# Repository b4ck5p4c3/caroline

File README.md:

# Project Caroline

Stratum 1 NTP server and clock reference based on surplus Huawei LMPT board.

**TBD**

## License

These licenses apply to this repository, unless otherwise noted:

- [MIT X11 License](./LICENSE) for software, configuration files, and documentation.
- [CERN-OHL-S](./hardware/LICENSE) for hardware design files.

## Acknowledgments

- <https://blog.heypete.com/2016/11/01/note-to-self-raspberry-pi-motorola-oncore-ut-setup/>
- <https://github.com/tiagofreire-pt/rpi_uputronics_stratum1_chrony>

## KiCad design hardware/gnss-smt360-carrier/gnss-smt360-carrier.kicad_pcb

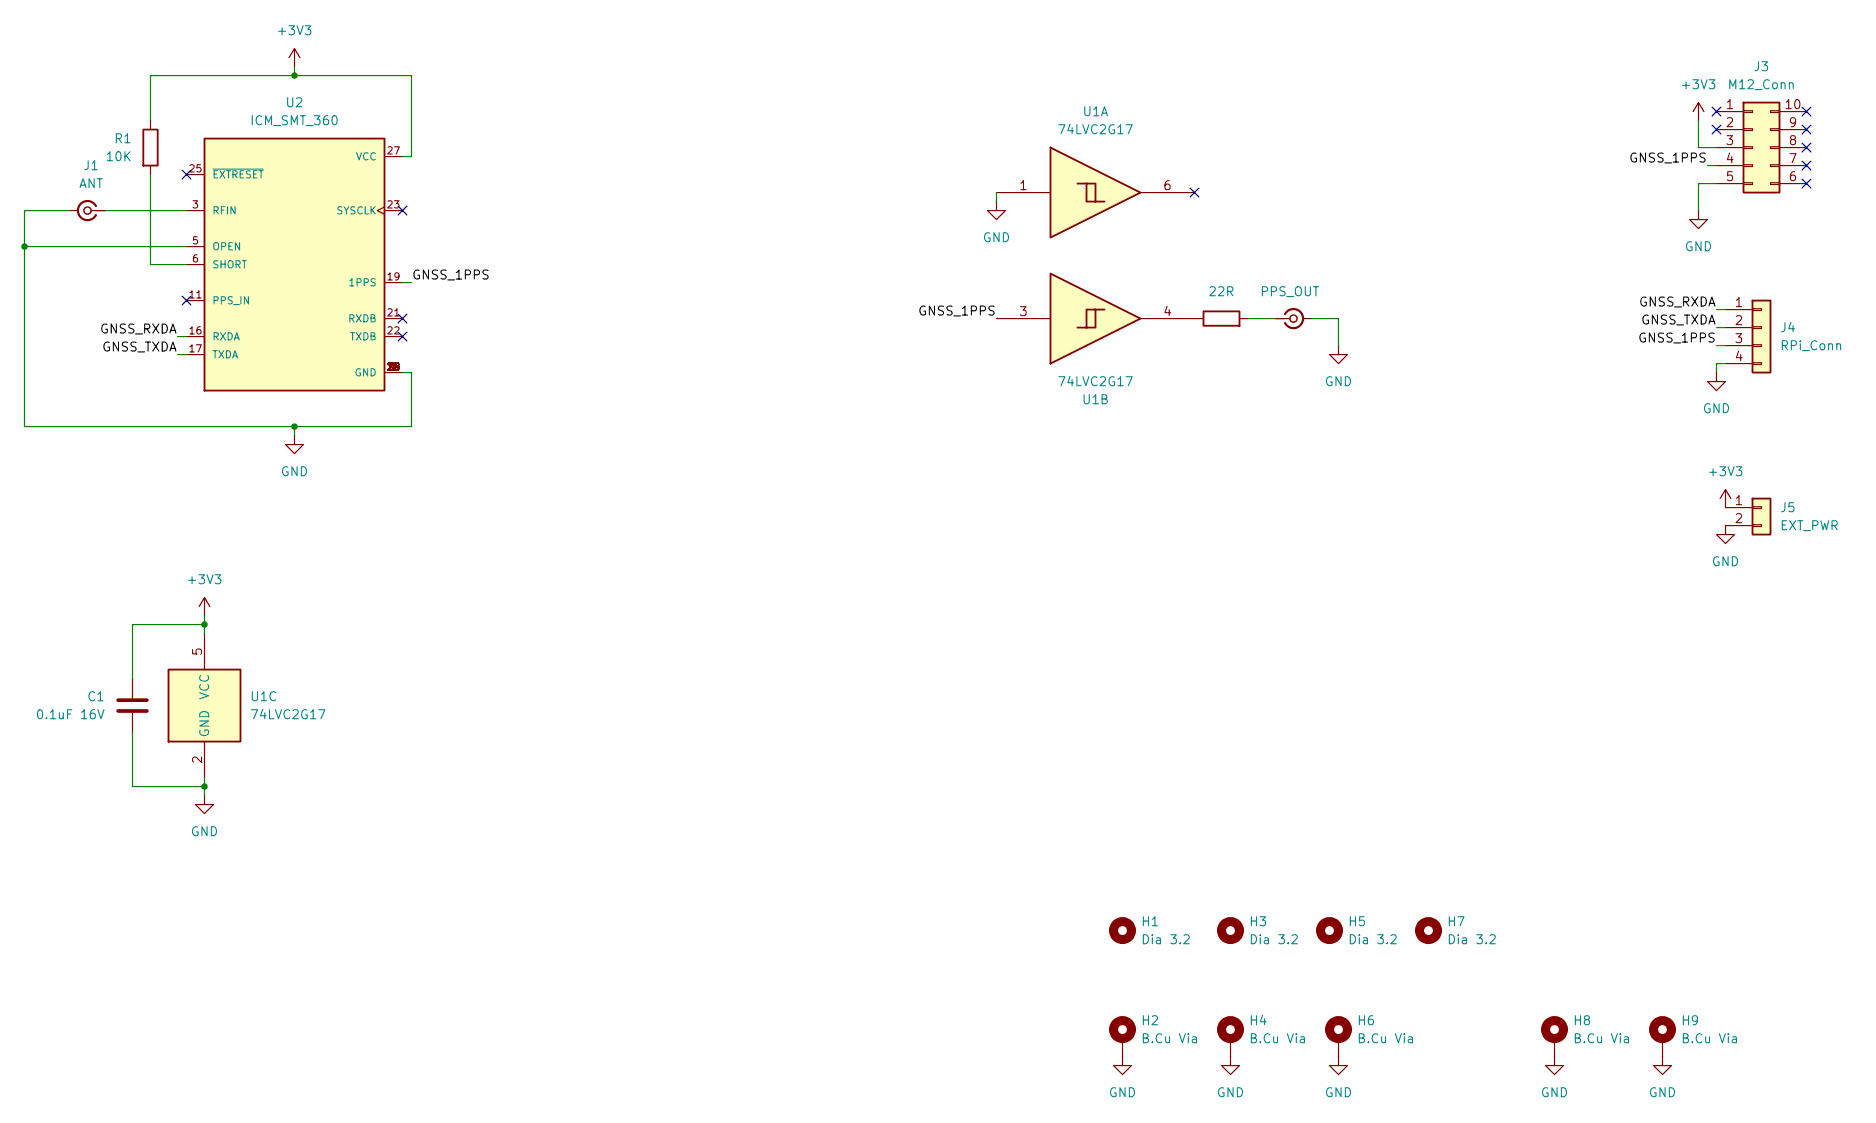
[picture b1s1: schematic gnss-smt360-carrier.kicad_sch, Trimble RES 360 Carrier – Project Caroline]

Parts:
C1: 0.1uF 16V; C_0805_2012Metric
H1, H3, H5, H7: Dia 3.2; MountingHole_3.2mm_M3
H2, H4, H6, H8, H9: B.Cu Via; Hole_Via_0.8mm
J1: ANT; SMA_Molex_73251-2200_Horizontal
J2: PPS_OUT; Connector_RF_UFL_SMT160
J3: M12_Conn; PinHeader_2x05_P1.27mm_Vertical_SMD
J4: RPi_Conn; PinHeader_1x04_P2.54mm_Vertical
J5: EXT_PWR; PinHeader_1x02_P2.54mm_Vertical
R1: 10K; R_0805_2012Metric
R2: 22R; R_0805_2012Metric
U1: 74LVC2G17; SOT-23-6
U2: ICM_SMT_360; RF_GPS_ICM_SMT_360; PARTREV G

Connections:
+3V3: C1.2, J3.3 (+3V_PWR), J5.1, R1.1, U1.5 (VCC), U2.27 (VCC)
/GNSS_1PPS: J3.4 (1PPS), J4.3, U1.3, U2.19 (1PPS)
/GNSS_RXDA: J4.1, U2.16 (RXDA)
/GNSS_TXDA: J4.2, U2.17 (TXDA)
GND: C1.1, H2.1, H4.1, H6.1, H8.1, H9.1, J1.2 (Ext), J2.2 (Ext), J3.5 (GND), J4.4, J5.2, U1.1, U1.2 (GND), U2.1 (GND), U2.2 (GND), U2.4 (GND), U2.5 (OPEN), U2.14 (GND), U2.15 (GND), U2.18 (GND), U2.20 (GND), U2.24 (GND), U2.26 (GND), U2.28 (GND)
unnamed: J1.1 (In), U2.3 (RFIN)
unnamed: J2.1 (In), R2.2
unnamed: R2.1, U1.4
unnamed: R1.2, U2.6 (SHORT)

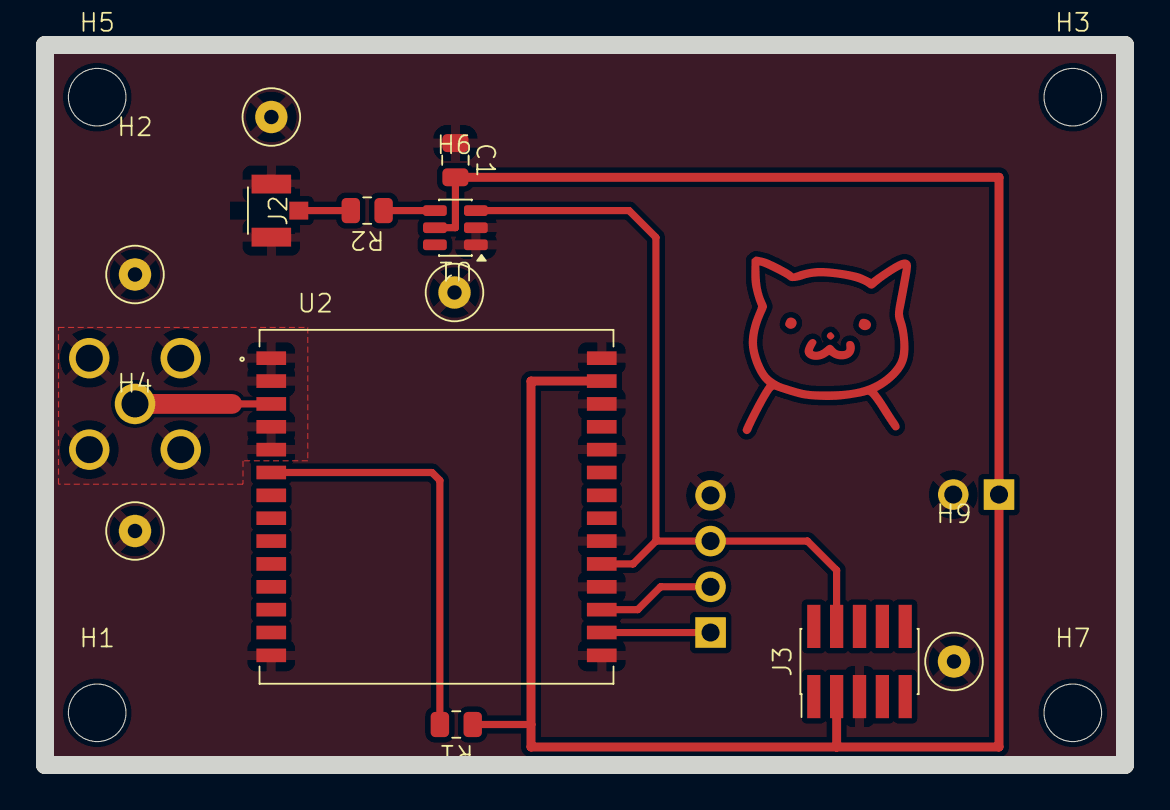
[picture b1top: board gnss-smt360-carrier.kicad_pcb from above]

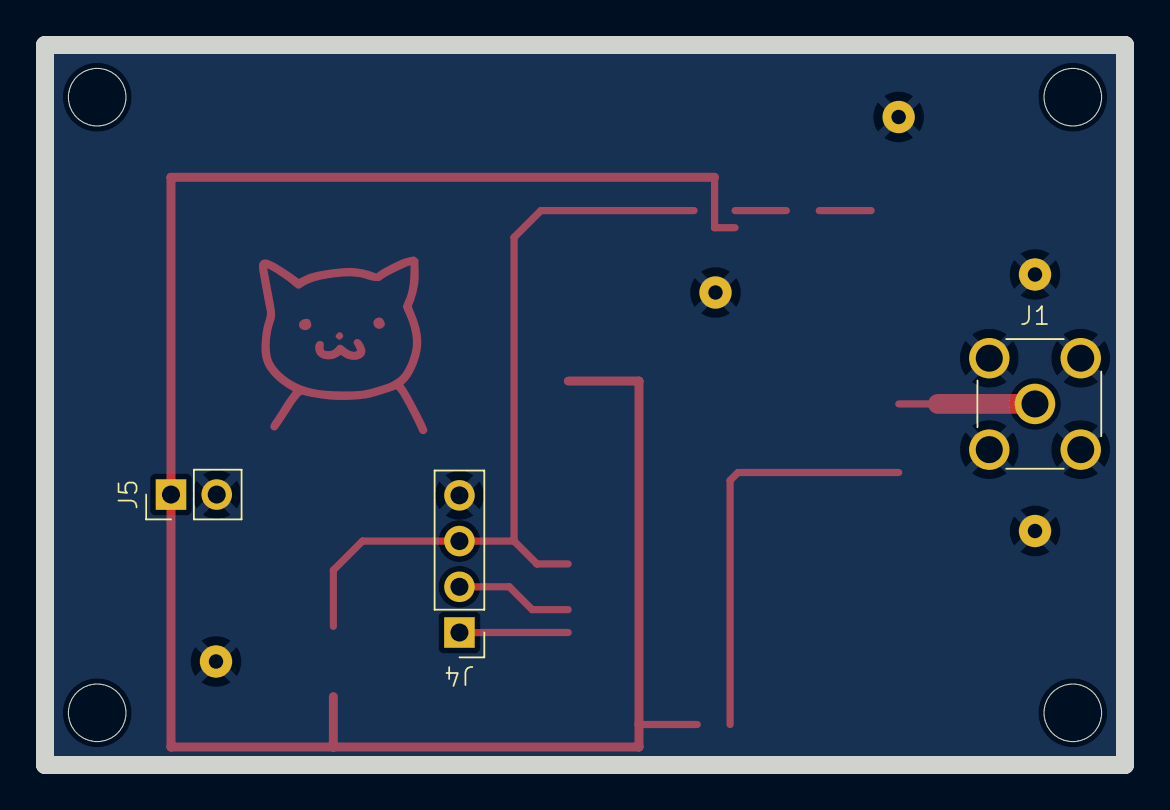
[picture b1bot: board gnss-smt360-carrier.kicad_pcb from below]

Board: 2 copper layers, 60.0 x 40.0 mm, 19 parts (3 on the bottom side), 9 nets.

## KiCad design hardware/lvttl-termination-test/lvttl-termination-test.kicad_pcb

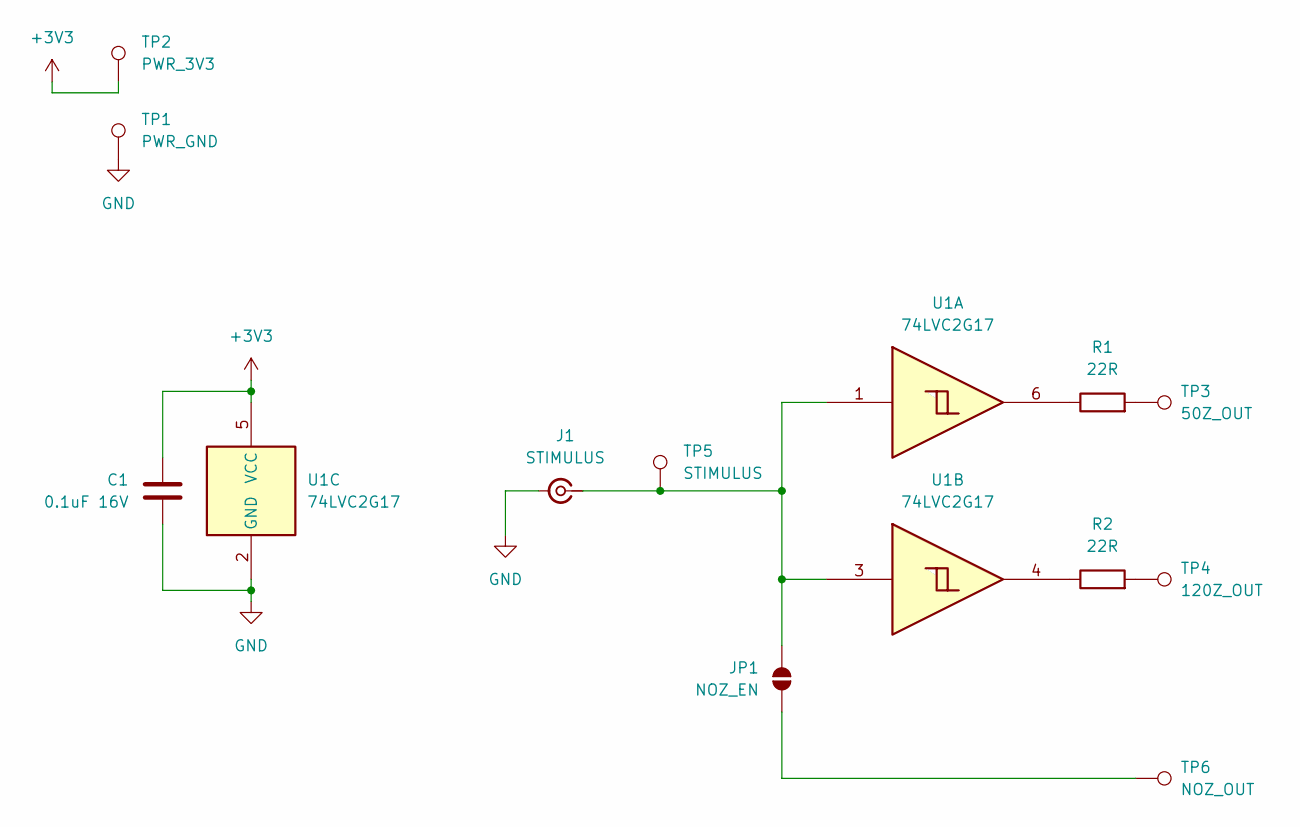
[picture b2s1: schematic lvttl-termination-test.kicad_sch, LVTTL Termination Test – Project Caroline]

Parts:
C1: 0.1uF 16V; C_0805_2012Metric
J1: STIMULUS; SMA_Molex_73251-1153_EdgeMount_Horizontal
JP1: NOZ_EN; SolderJumper-2_P1.3mm_Open_TrianglePad1.0x1.5mm
R1, R2: 22R; R_0805_2012Metric
TP1: PWR_GND; TestPoint_Pad_1.5x1.5mm
TP2: PWR_3V3; TestPoint_Pad_D1.5mm
TP3: 50Z_OUT; TestPoint_Pad_D1.5mm
TP4: 120Z_OUT; TestPoint_Pad_D1.5mm
TP5: STIMULUS; TestPoint_Pad_D1.5mm
TP6: NOZ_OUT; TestPoint_Pad_D1.5mm
U1: 74LVC2G17; SOT-23-6

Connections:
+3V3: C1.1, TP2.1, U1.5 (VCC)
GND: C1.2, J1.2 (Ext), TP1.1, U1.2 (GND)
unnamed: J1.1 (In), JP1.2 (B), TP5.1, U1.1, U1.3
unnamed: JP1.1 (A), TP6.1
unnamed: R1.1, U1.6
unnamed: R1.2, TP3.1
unnamed: R2.1, U1.4
unnamed: R2.2, TP4.1

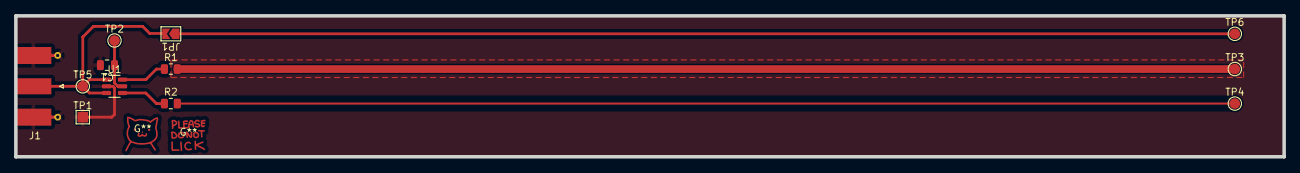
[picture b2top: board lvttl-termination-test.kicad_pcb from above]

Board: 2 copper layers, 180.0 x 20.0 mm, 14 parts (0 on the bottom side), 8 nets.

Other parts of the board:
G**: Cat; Flo_Cat_Image
G**#2: DNL; Flo_DNL_Image

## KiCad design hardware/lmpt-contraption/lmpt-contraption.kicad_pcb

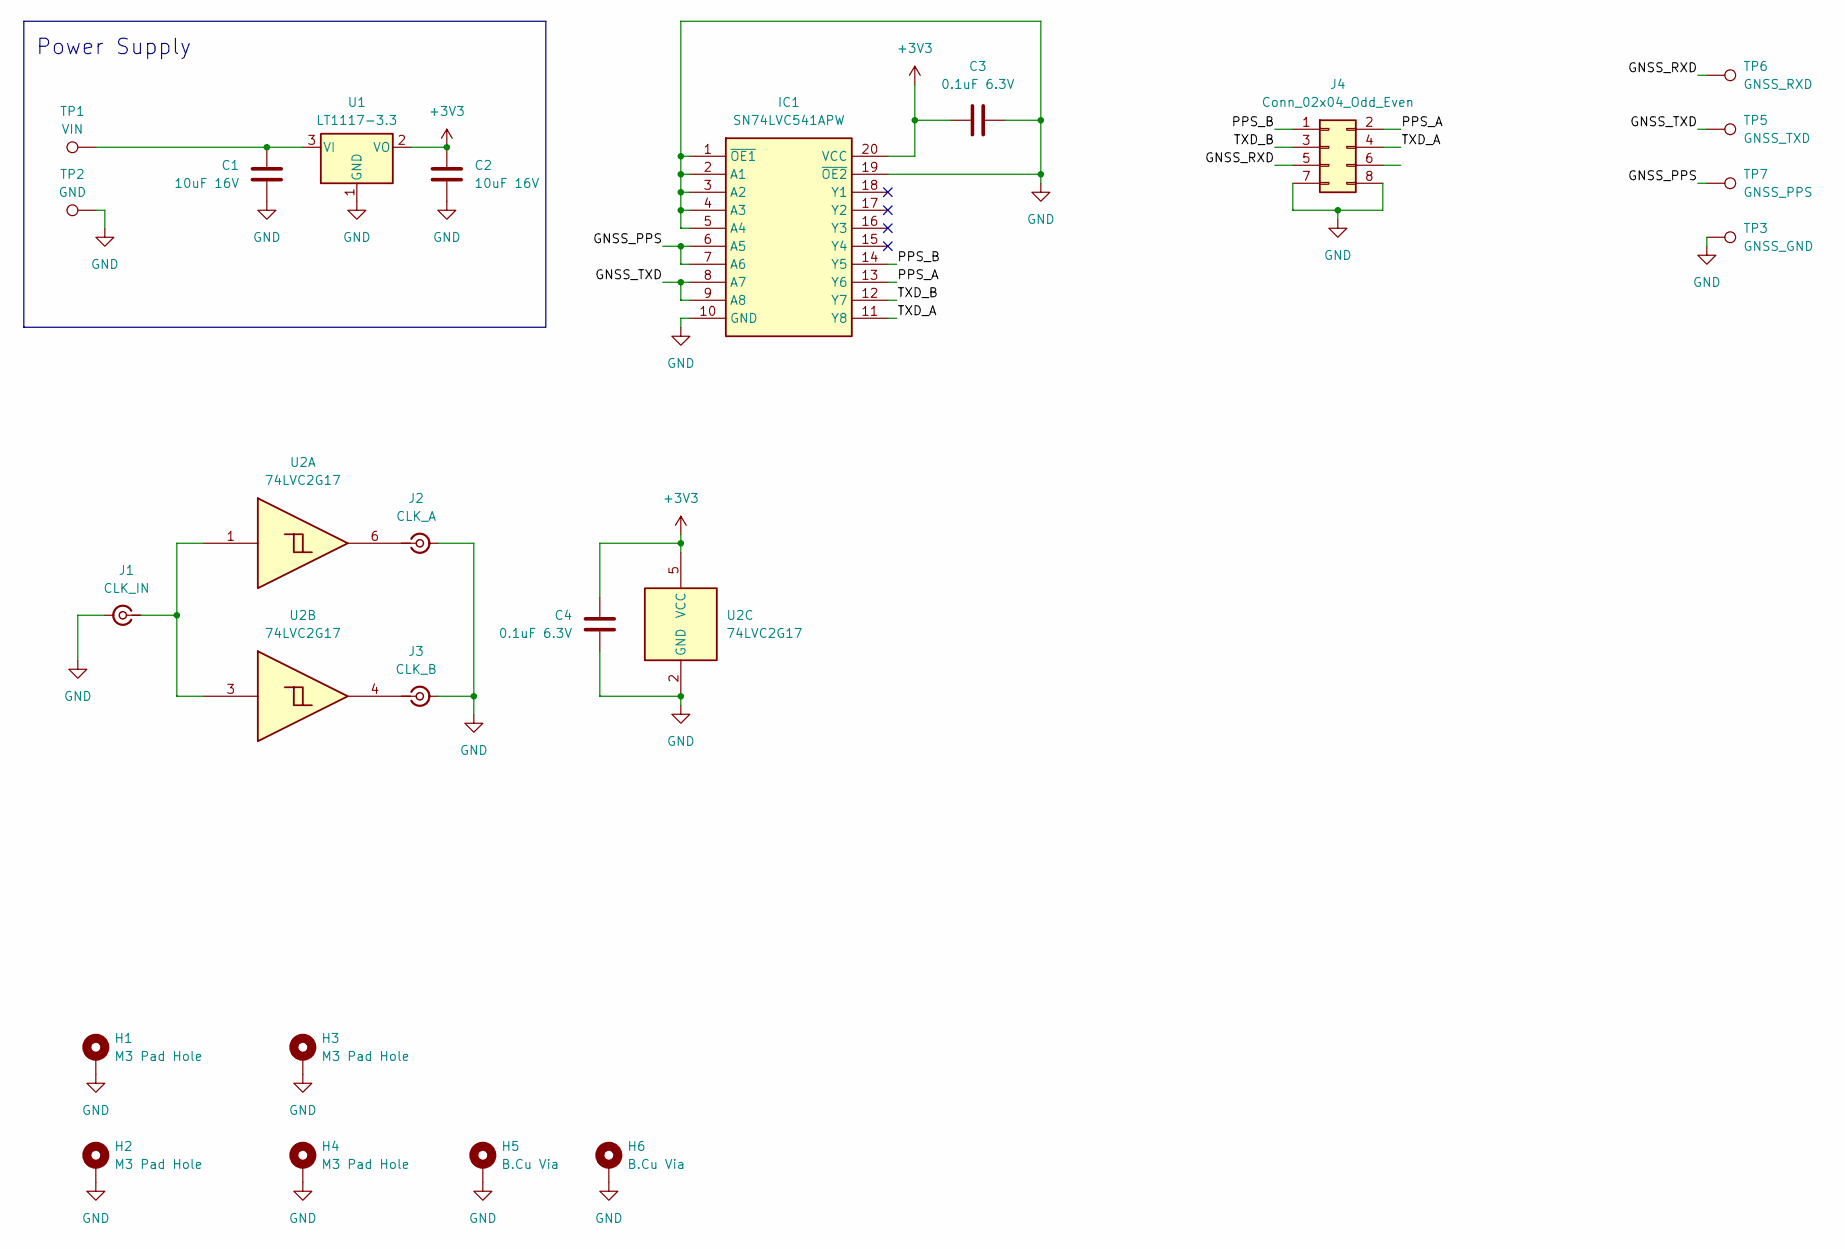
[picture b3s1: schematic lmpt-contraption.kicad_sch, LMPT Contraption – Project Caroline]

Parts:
C1, C2: 10uF 16V; C_0805_2012Metric
C3, C4: 0.1uF 6.3V; C_0805_2012Metric
H1, H2, H3, H4: M3 Pad Hole; MountingHole_3.2mm_M3_Pad_TopBottom
H5, H6: B.Cu Via; Hole_Via_0.8mm
IC1: SN74LVC541APW; TSSOP-20_4.4x6.5mm_P0.65mm; Mouser Part Number 595-SN74LVC541APW
J1: CLK_IN; Connector_RF_UFL_SMT160
J2: CLK_A; SMA_Molex_73251-1153_EdgeMount_Horizontal
J3: CLK_B; SMA_Molex_73251-1153_EdgeMount_Horizontal
J4: Conn_02x04_Odd_Even; PinSocket_2x04_P2.54mm_Vertical_SMD
TP1: VIN; BKSP_TestPoint_Pad_5mm_2.5mm
TP2: GND; BKSP_TestPoint_Pad_5mm_2.5mm
TP3: GNSS_GND; BKSP_TestPoint_Pad_5mm_2.5mm
TP5: GNSS_TXD; BKSP_TestPoint_Pad_5mm_2.5mm
TP6: GNSS_RXD; BKSP_TestPoint_Pad_5mm_2.5mm
TP7: GNSS_PPS; BKSP_TestPoint_Pad_5mm_2.5mm
U1: LT1117-3.3; SOT-223-3_TabPin2
U2: 74LVC2G17; SOT-23-6

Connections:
+3V3: C2.1, C3.2, C4.1, IC1.20 (VCC), U1.2 (VO), U2.5 (VCC)
/GNSS_PPS: IC1.6 (A5), IC1.7 (A6), TP7.1
/GNSS_RXD: J4.5, TP6.1
/GNSS_TXD: IC1.8 (A7), IC1.9 (A8), TP5.1
/PPS_A: IC1.13 (Y6), J4.2
/PPS_B: IC1.14 (Y5), J4.1
/TXD_A: IC1.11 (Y8), J4.4
/TXD_B: IC1.12 (Y7), J4.3
GND: C1.2, C2.2, C3.1, C4.2, H1.1, H2.1, H3.1, H4.1, H5.1, H6.1, IC1.1 (~OE1), IC1.2 (A1), IC1.3 (A2), IC1.4 (A3), IC1.5 (A4), IC1.10 (GND), IC1.19 (~OE2), J1.2 (Ext), J2.2 (Ext), J3.2 (Ext), J4.7, J4.8, TP2.1, TP3.1, U1.1 (GND), U2.2 (GND)
unnamed: J1.1 (In), U2.1, U2.3
unnamed: J2.1 (In), U2.6
unnamed: J3.1 (In), U2.4
unnamed: C1.1, TP1.1, U1.3 (VI)

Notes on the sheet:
Power Supply

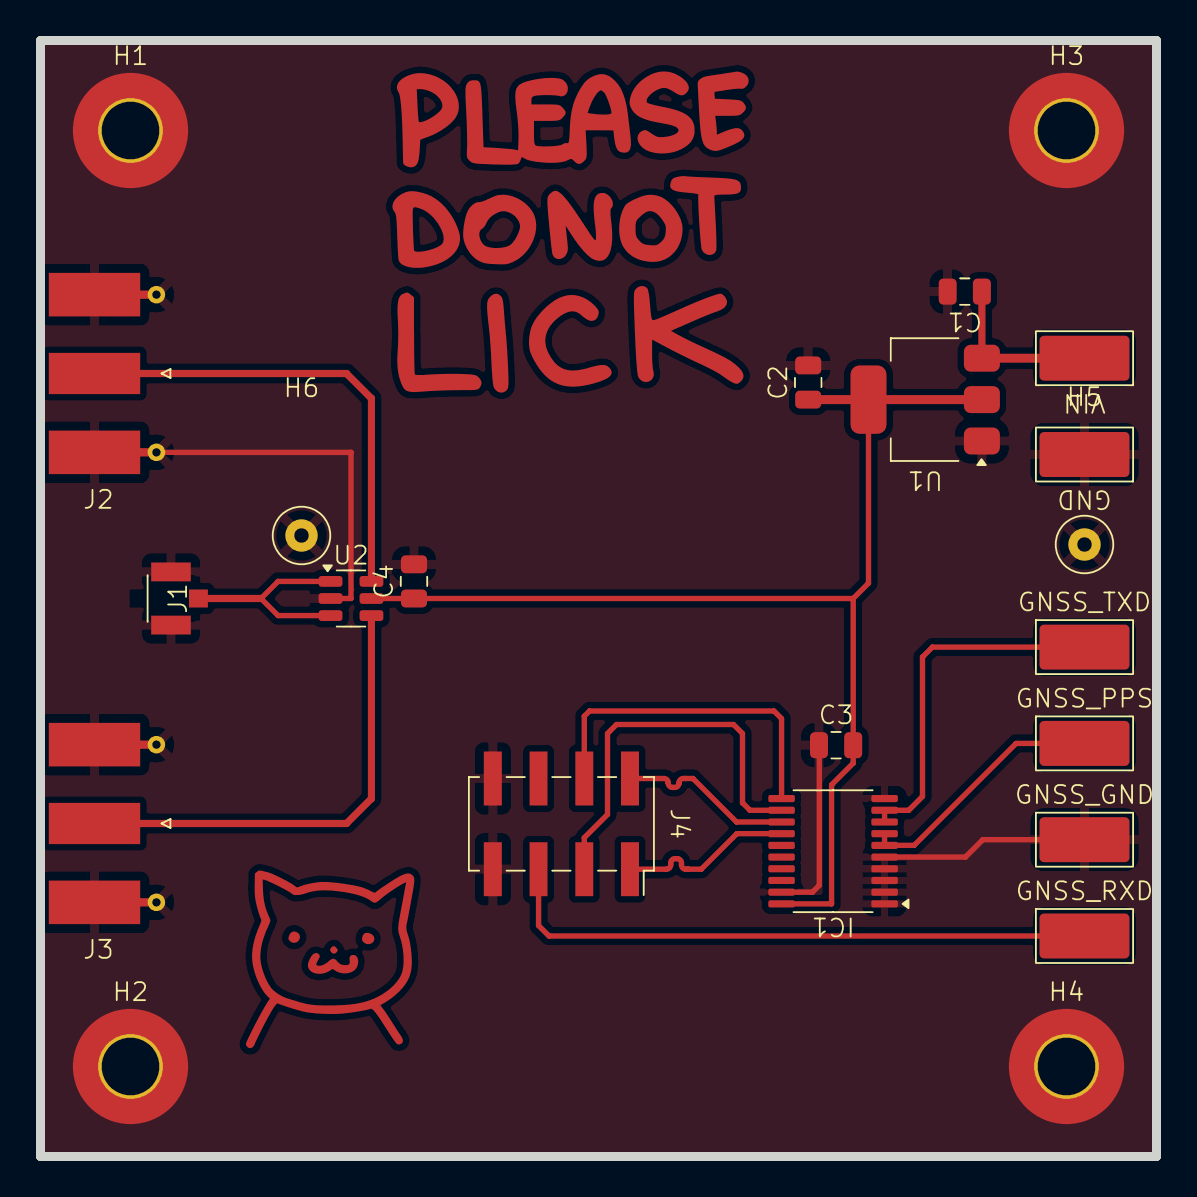
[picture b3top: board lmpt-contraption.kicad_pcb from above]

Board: 2 copper layers, 62.0 x 62.0 mm, 23 parts (0 on the bottom side), 13 nets.

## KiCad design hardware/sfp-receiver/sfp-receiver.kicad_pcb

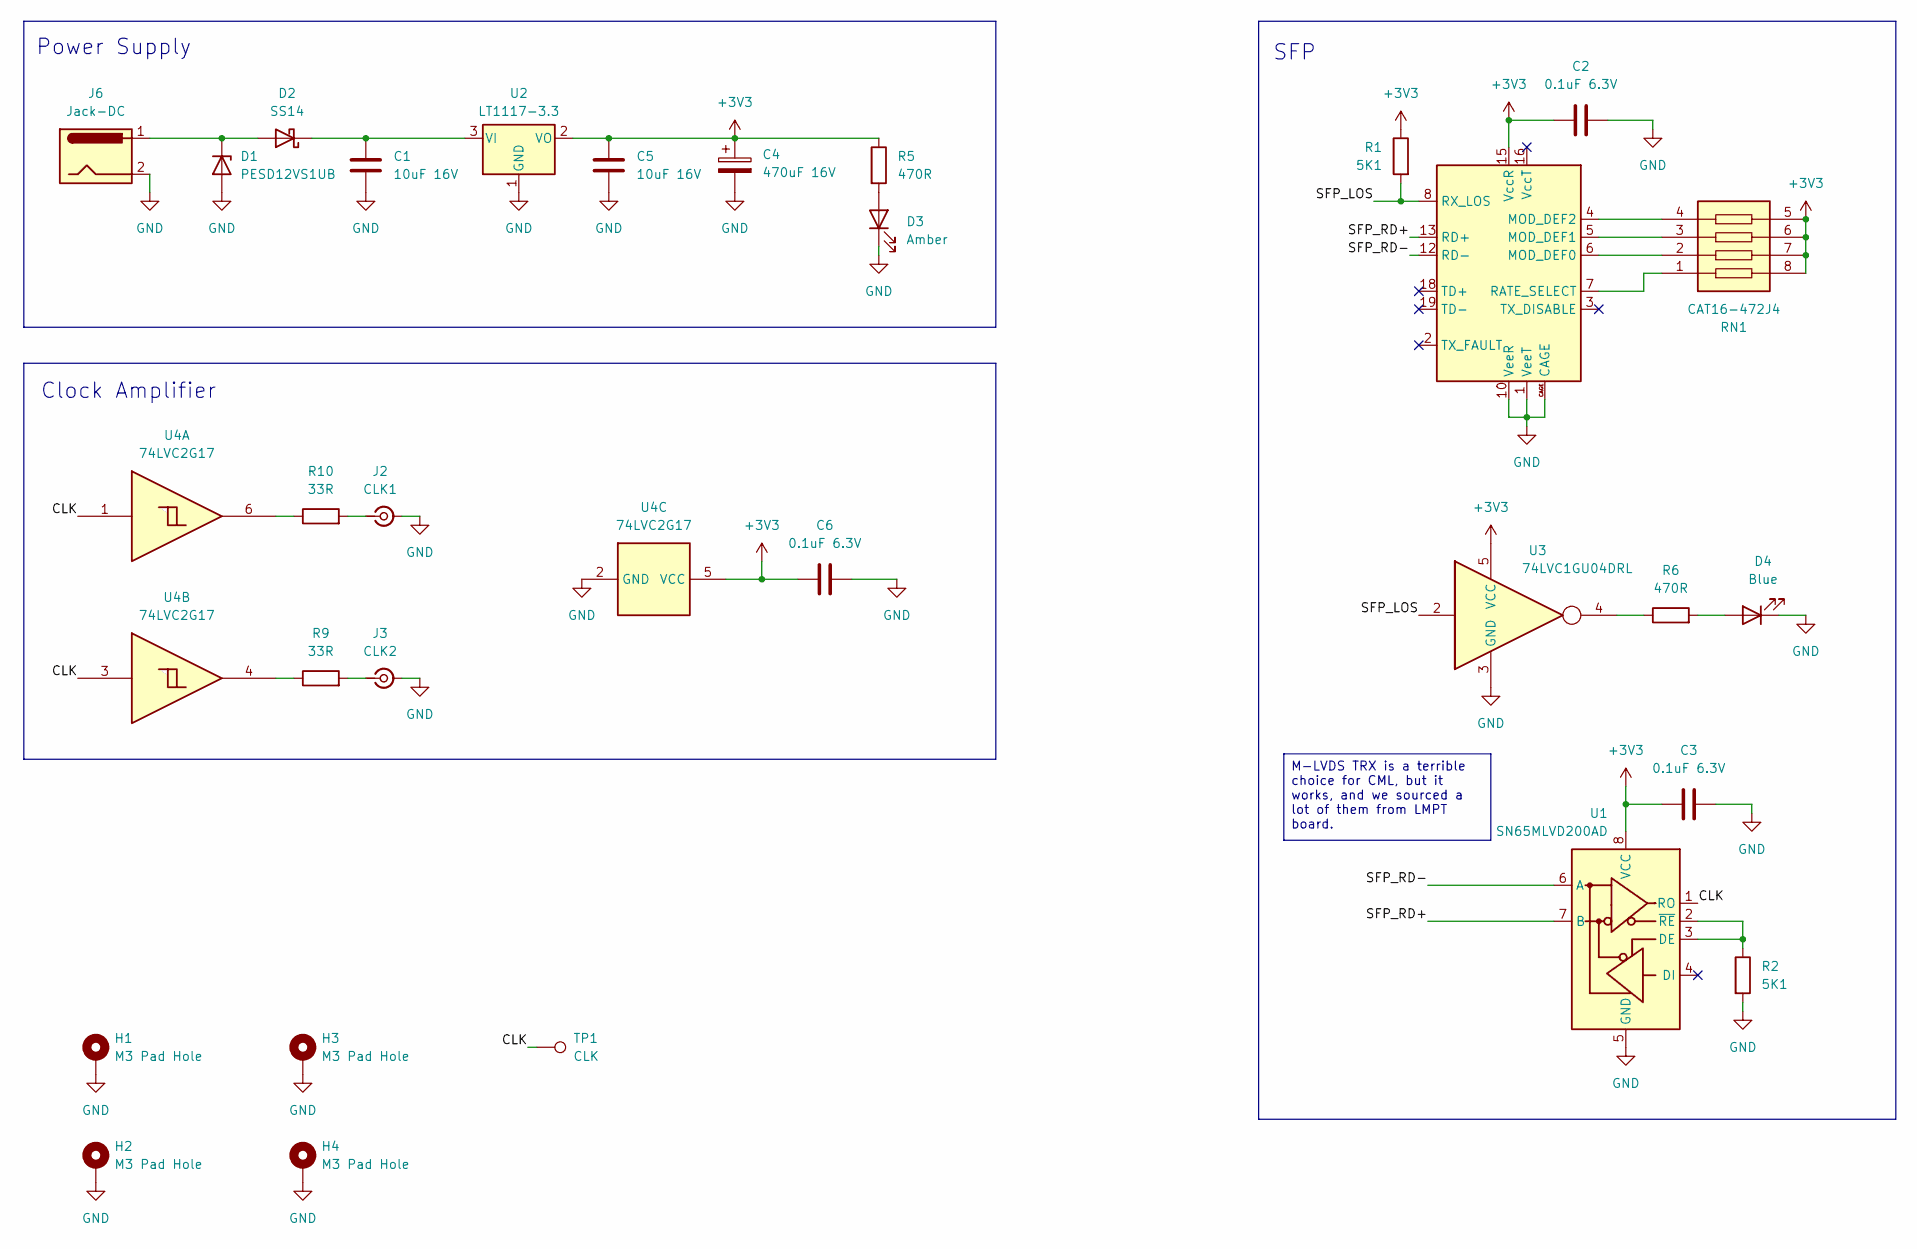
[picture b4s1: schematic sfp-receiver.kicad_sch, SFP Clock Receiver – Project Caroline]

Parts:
C1, C5: 10uF 16V; C_0805_2012Metric
C2, C3, C6: 0.1uF 6.3V; C_0805_2012Metric
C4: 470uF 16V; C_Elec_10x10.2
D1: PESD12VS1UB; D_SOD-523
D2: SS14; D_SMA
D3: Amber; LED_1206_3216Metric
D4: Blue; LED_1206_3216Metric
H1, H2, H3, H4: M3 Pad Hole; MountingHole_3.2mm_M3_Pad_TopBottom
J1: SFP; Connector_SFP_Cage_NoKeepout
J2: CLK1; SMA_Amphenol_132203-12_Horizontal
J3: CLK2; SMA_Amphenol_132203-12_Horizontal
J6: Jack-DC; BarrelJack_Horizontal
R1, R2: 5K1; R_0805_2012Metric
R5, R6: 470R; R_0805_2012Metric
R9, R10: 33R; R_0805_2012Metric
RN1: CAT16-472J4; R_Array_Concave_4x0603; Mouser Part Number 652-CAT16-4.7K
TP1: CLK; TestPoint_Pad_D1.5mm
U1: SN65MLVD200AD; SOIC-8_3.9x4.9mm_P1.27mm
U2: LT1117-3.3; SOT-223-3_TabPin2
U3: 74LVC1GU04DRL; SOT-553
U4: 74LVC2G17; SOT-23-6

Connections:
+3V3: C2.1, C3.1, C4.1, C5.1, C6.1, J1.15 (VccR), R1.1, R5.1, RN1.5, RN1.6, RN1.7, RN1.8, U1.8 (VCC), U2.2 (VO), U3.5 (VCC), U4.5 (VCC)
/CLK: TP1.1, U1.1 (RO), U4.1, U4.3
/SFP_LOS: J1.8 (RX_LOS), R1.2, U3.2
/SFP_RD+: J1.13 (RD+), U1.7 (B); also elsewhere on the board
/SFP_RD-: J1.12 (RD-), U1.6 (A)
GND: C1.2, C2.2, C3.2, C4.2, C5.2, C6.2, D1.2 (A), D3.1 (K), D4.1 (K), H1.1, H2.1, H3.1, H4.1, J1.1 (VeeT), J1.9 (VeeR), J1.10 (VeeR), J1.11 (VeeR), J1.14 (VeeR), J1.17 (VeeT), J1.20 (VeeT), J1.CAGE, J2.2 (Ext), J3.2 (Ext), J6.2, R2.2, U1.5 (GND), U2.1 (GND), U3.3 (GND), U4.2 (GND); also elsewhere on the board
unnamed: D1.1 (K), D2.2 (A), J6.1
unnamed: C1.1, D2.1 (K), U2.3 (VI)
unnamed: D3.2 (A), R5.2
unnamed: D4.2 (A), R6.2
unnamed: J1.6 (MOD_DEF0), RN1.2
unnamed: J1.5 (MOD_DEF1), RN1.3
unnamed: J1.4 (MOD_DEF2), RN1.4
unnamed: J1.7 (RATE_SELECT), RN1.1
unnamed: J2.1 (In), R10.2
unnamed: J3.1 (In), R9.2
unnamed: R6.1, U3.4
unnamed: R9.1, U4.4
unnamed: R10.1, U4.6
unnamed: R2.1, U1.2 (~RE), U1.3 (DE)

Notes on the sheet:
Power Supply
Clock Amplifier
SFP
M-LVDS TRX is a terrible choice for CML, but it works, and we sourced a lot of them from LMPT board.

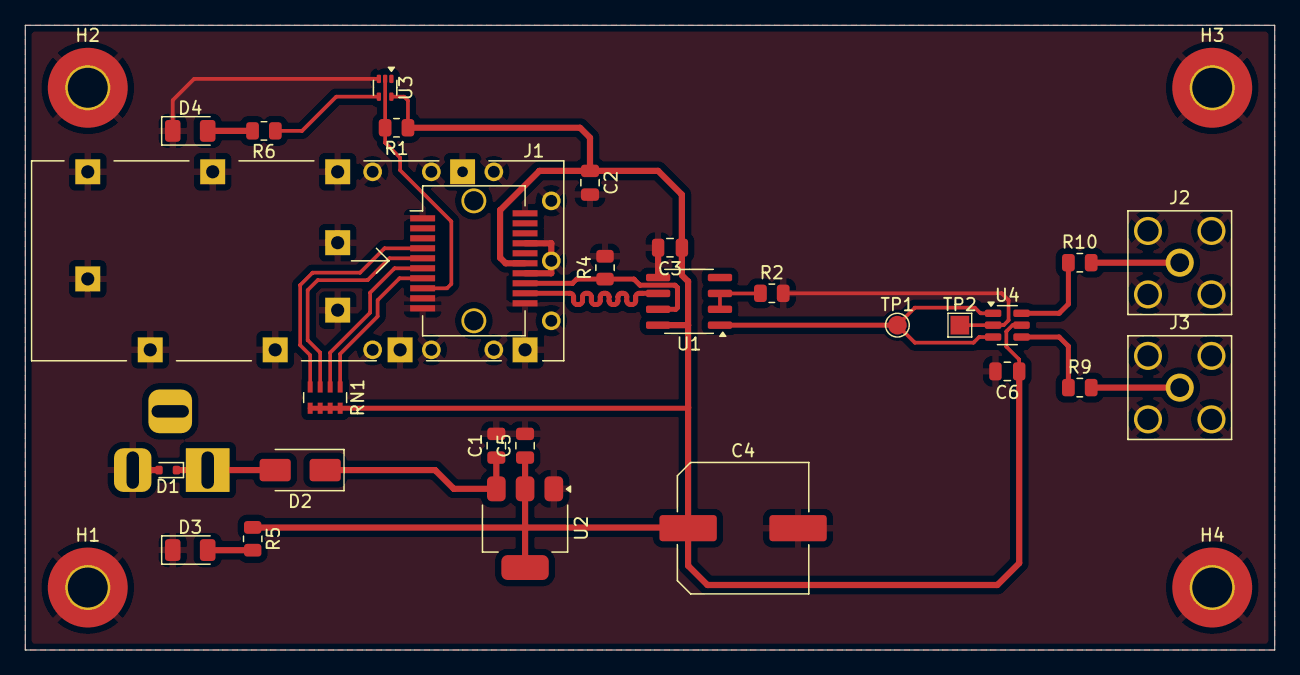
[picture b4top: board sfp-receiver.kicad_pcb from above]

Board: 2 copper layers, 100.0 x 50.0 mm, 32 parts (1 on the bottom side), 20 nets.

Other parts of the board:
R4: 100K; R_0805_2012Metric
TP2: GND; TestPoint_Pad_1.5x1.5mm

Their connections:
/SFP_RD+: R4.1; also elsewhere on the board
GND: R4.2, TP2.1; also elsewhere on the board

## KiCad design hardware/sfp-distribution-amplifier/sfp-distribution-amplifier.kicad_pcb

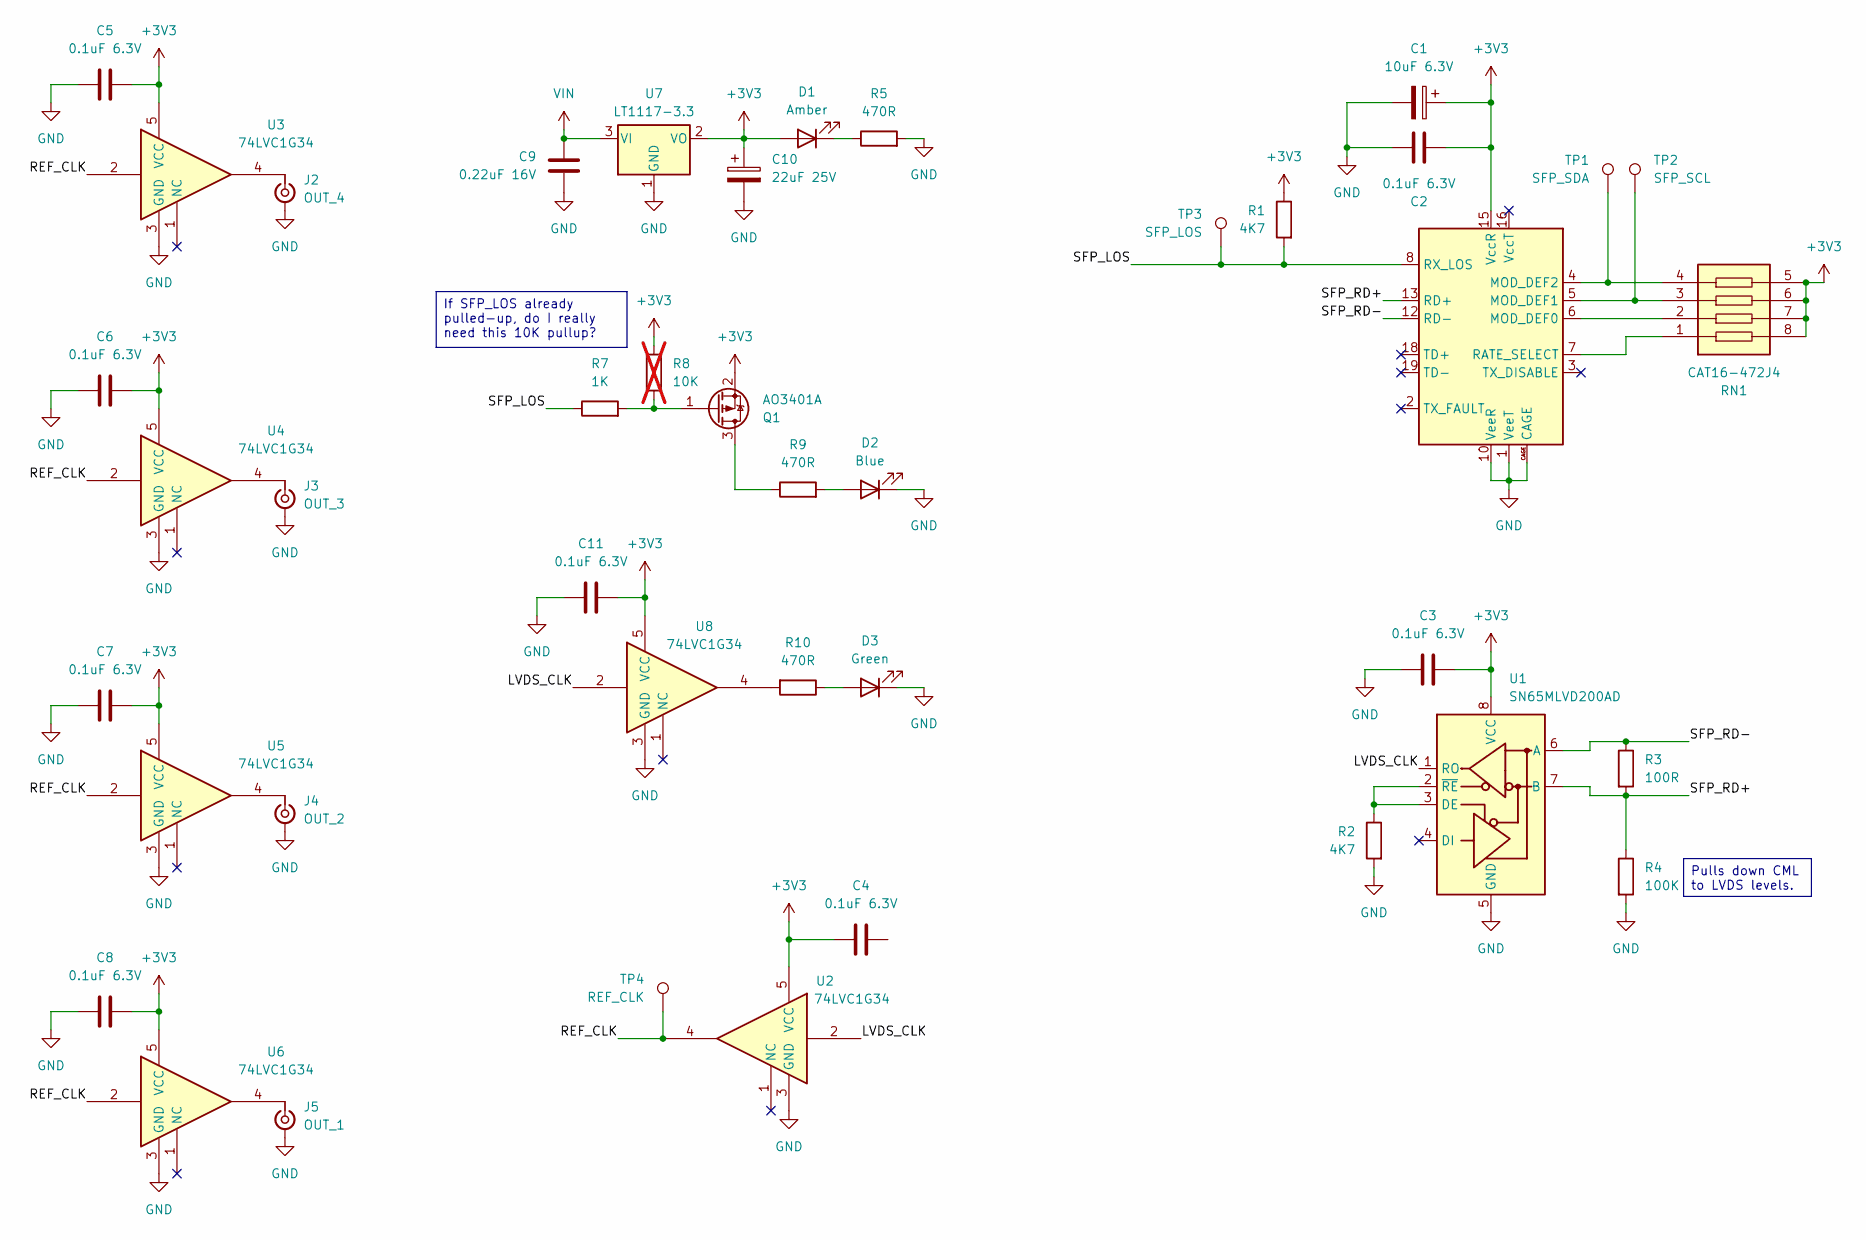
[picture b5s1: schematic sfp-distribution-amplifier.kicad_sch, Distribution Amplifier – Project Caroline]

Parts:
C1: 10uF 6.3V; CP_Elec_4x3
C2, C3, C4, C5, C6, C7, C8, C11: 0.1uF 6.3V; C_0805_2012Metric
C9: 0.22uF 16V; C_0805_2012Metric
C10: 22uF 25V; C_1206_3216Metric
D1: Amber; LED_1206_3216Metric
D2: Blue; LED_1206_3216Metric
D3: Green; LED_1206_3216Metric
J1: SFP; Connector_SFP_Cage_NoKeepout
J2: OUT_4; SMA_Amphenol_132203-12_Horizontal
J3: OUT_3; SMA_Amphenol_132203-12_Horizontal
J4: OUT_2; SMA_Amphenol_132203-12_Horizontal
J5: OUT_1; SMA_Amphenol_132203-12_Horizontal
Q1: AO3401A; SOT-23
R1, R2: 4K7; R_0805_2012Metric
R3: 100R; R_0805_2012Metric
R4: 100K; R_0805_2012Metric
R5, R9, R10: 470R; R_0805_2012Metric
R7: 1K; R_1206_3216Metric
R8: 10K; R_0805_2012Metric; not fitted
RN1: CAT16-472J4; R_Array_Concave_4x0603; Mouser Part Number 652-CAT16-4.7K
TP1: SFP_SDA; TestPoint_Pad_1.0x1.0mm
TP2: SFP_SCL; TestPoint_Pad_D1.0mm
TP3: SFP_LOS; TestPoint_Pad_D1.0mm
TP4: REF_CLK; TestPoint_Pad_D1.0mm
U1: SN65MLVD200AD; SOIC-8_3.9x4.9mm_P1.27mm
U2, U3, U4, U5, U6, U8: 74LVC1G34; SOT-23-5
U7: LT1117-3.3; SOT-223-3_TabPin2

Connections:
+3V3: C1.1, C2.1, C3.1, C4.2, C5.2, C6.2, C7.2, C8.2, C10.1, C11.2, D1.2 (A), J1.15 (VccR), Q1.2 (S), R1.1, R8.2, RN1.5, RN1.6, RN1.7, RN1.8, U1.8 (VCC), U2.5 (VCC), U3.5 (VCC), U4.5 (VCC), U5.5 (VCC), U6.5 (VCC), U7.2 (VO), U8.5 (VCC)
/LVDS_CLK: U1.1 (RO), U2.2, U8.2
/REF_CLK: TP4.1, U2.4, U3.2, U4.2, U5.2, U6.2
/SFP_LOS: J1.8 (RX_LOS), R1.2, R7.1, TP3.1
/SFP_RD+: J1.13 (RD+), R3.2, R4.1, U1.7 (B)
/SFP_RD-: J1.12 (RD-), R3.1, U1.6 (A)
GND: C1.2, C2.2, C3.2, C5.1, C6.1, C7.1, C8.1, C9.2, C10.2, C11.1, D2.1 (K), D3.1 (K), J1.1 (VeeT), J1.9 (VeeR), J1.10 (VeeR), J1.11 (VeeR), J1.14 (VeeR), J1.17 (VeeT), J1.20 (VeeT), J1.CAGE, J2.2 (Ext), J3.2 (Ext), J4.2 (Ext), J5.2 (Ext), R2.2, R4.2, R5.2, U1.5 (GND), U2.3 (GND), U3.3 (GND), U4.3 (GND), U5.3 (GND), U6.3 (GND), U7.1 (GND), U8.3 (GND)
unnamed: D1.1 (K), R5.1
unnamed: D2.2 (A), R9.2
unnamed: D3.2 (A), R10.1
unnamed: J1.6 (MOD_DEF0), RN1.2
unnamed: J1.5 (MOD_DEF1), RN1.3, TP2.1
unnamed: J1.4 (MOD_DEF2), RN1.4, TP1.1
unnamed: J1.7 (RATE_SELECT), RN1.1
unnamed: J2.1 (In), U3.4
unnamed: J3.1 (In), U4.4
unnamed: J4.1 (In), U5.4
unnamed: J5.1 (In), U6.4
unnamed: Q1.3 (D), R9.1
unnamed: Q1.1 (G), R7.2, R8.1
unnamed: R10.2, U8.4
unnamed: R2.1, U1.2 (~RE), U1.3 (DE)
VIN: C9.1, U7.3 (VI)

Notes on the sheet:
Pulls down CML to LVDS levels.
If SFP_LOS already pulled-up, do I really need this 10K pullup?

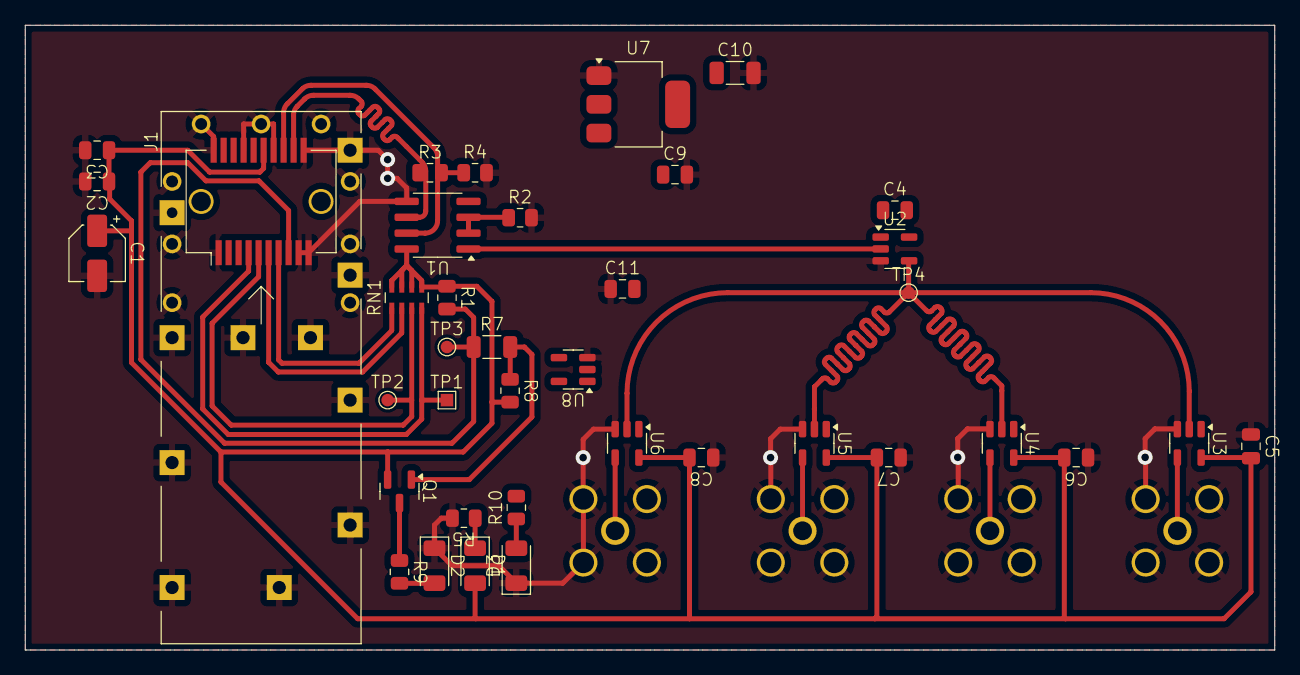
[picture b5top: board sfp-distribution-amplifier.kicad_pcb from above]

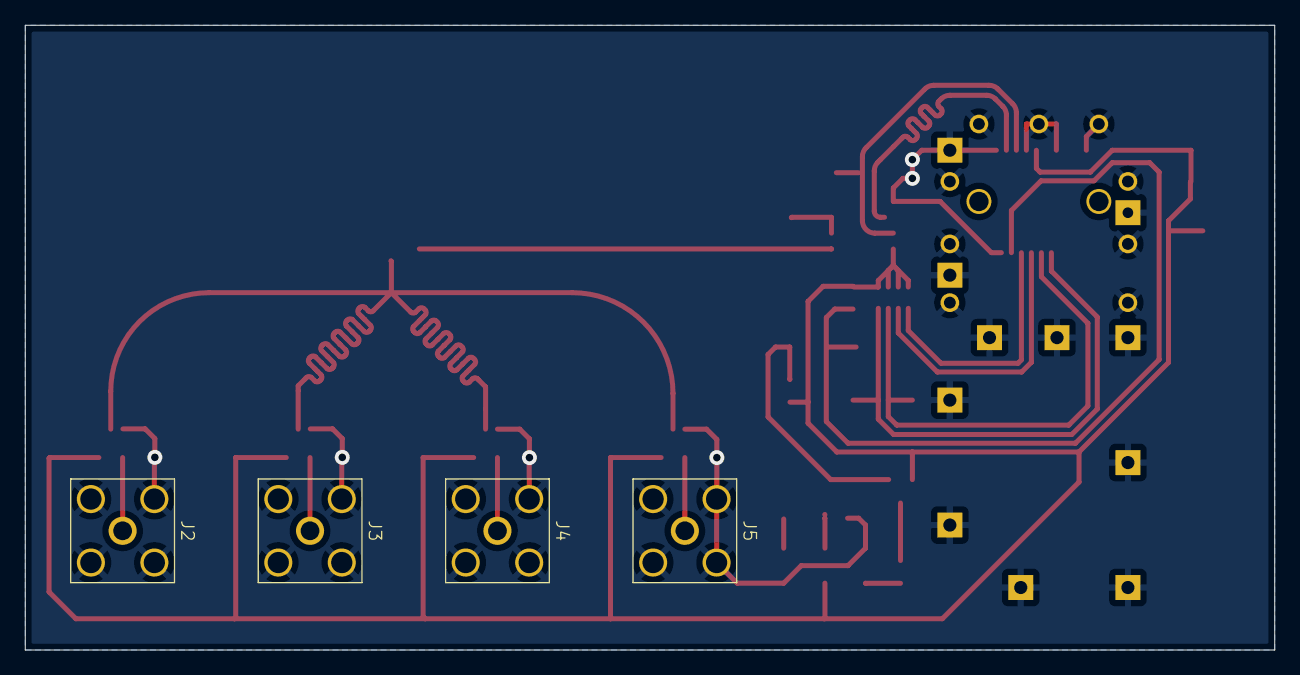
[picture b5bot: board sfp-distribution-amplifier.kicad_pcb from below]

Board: 2 copper layers, 100.0 x 50.0 mm, 42 parts (4 on the bottom side), 23 nets.

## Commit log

2025-04-26 feat(sfp-da): incomplete test revision
2025-05-01 feat(sfp-tx/rx-dev): manufactured rev. A
2025-07-28 feat(LMPT-contraption): revision A
2025-07-30 feat(LMPT-contraption): revision B
2025-08-22 feat(LMTP-contraption): Revision E
2025-08-22 feat(software/os): include crucial system configuration files
2025-08-22 docs: add README
2025-08-22 docs: fix incorrect license name
2025-09-05 feat(sw/exporter): add oncore-exporter
2025-09-05 fix(sw/exporter): fix serial path
2025-09-05 feat(sw/exporter): include systemd service
2025-09-08 feat(sw/pps-to-irig): add pps-to-irig service
2025-10-07 feat(os): update ntpsec conf
2025-10-07 feat(hw/test): add LVTTL termination test board
2025-10-07 feat(hw/gnss-smt360-carrier): add RES SMT 360 carrier test board in M12 format
2025-11-20 feat: add ntpsec reload wrapper
